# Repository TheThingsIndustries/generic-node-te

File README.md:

# Generic Node Tracker Edition (GNTE)

## About

The Generic Node Tracker Edition provides a reference HW design that features [Semtech LR1110](https://www.semtech.com/products/wireless-rf/lora-edge/lr1110) modem and an STM32L073 host MCU.

This repository contains all the necessary hardware and software files for the GNTE node.

## Documentation

The [Generic Node documentation website](https://www.genericnode.com/docs/) provides information about the node hardware and software features.

## Acknowledgment

The [Software](./Software) featured in this repository is a fork of Semtech [lr1110_modem_application_example](https://github.com/Lora-net/lr1110_modem_application_example) with minor changes that reflect the HW design.

## Legal

[Generic Node license terms and conditions](./LICENSE.md) apply.

[Contact The Things Industries](https://thethingsindustries.com/contact/) for licensing.

Copyright © 2021 The Things Industries B.V.

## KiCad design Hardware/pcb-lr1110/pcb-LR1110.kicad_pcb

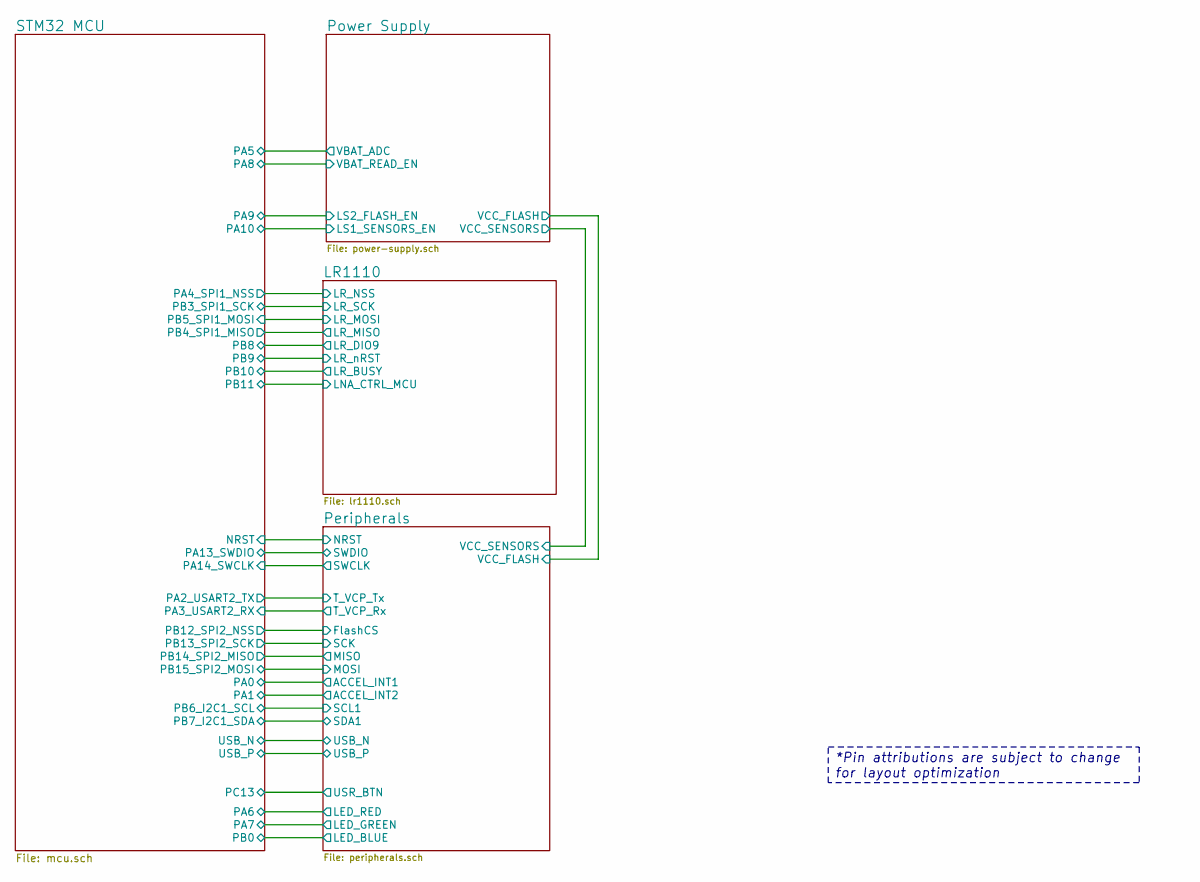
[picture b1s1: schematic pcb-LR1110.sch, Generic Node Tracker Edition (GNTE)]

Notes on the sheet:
*Pin attributions are subject to change for layout optimization

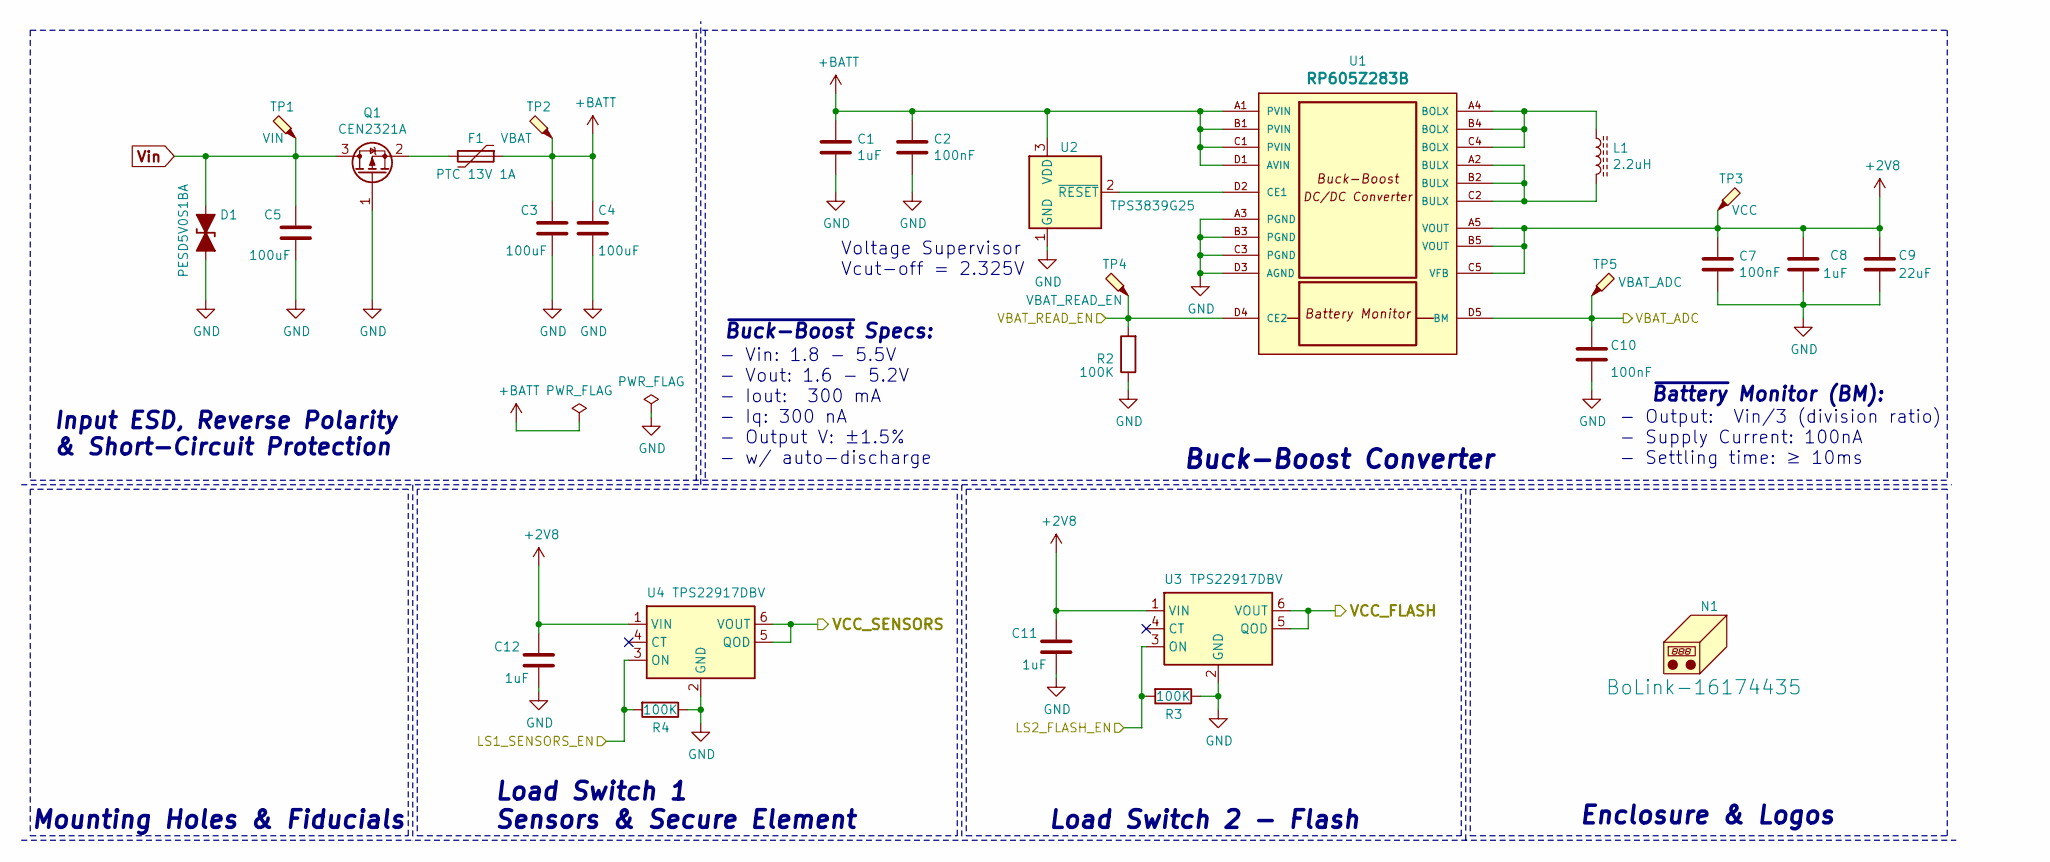
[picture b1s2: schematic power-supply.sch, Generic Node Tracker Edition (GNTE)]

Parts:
C1, C8, C11, C12: 1uF; C_0402_1005Metric; MPN CL05A105KQ5NNNC
C2, C7, C10: 100nF; C_0402_1005Metric; MPN CC0402KRX7R7BB104
C3, C4, C5: 100uF; C_1206_3216Metric; MPN JMK316ABJ107ML-T
C9: 22uF; C_0603_1608Metric; MPN CC0603MRX5R5BB226
D1: PESD5V0S1BA; D_SOD-323; MPN PESD5V0S1BA,115
F1: PTC 13V 1A; Fuse_1210_3225Metric_Castellated; MPN SMD1210-050
L1: 2.2uH; L_HPC4012TF-2R2M; MPN HPC4012TF-2R2M
N1: BoLink-16174435; BoLink_704025; MPN DNM
Q1: CEN2321A; SOT-23; MPN CEN2321A
R2, R3, R4: 100K; R_0402_1005Metric; MPN RC0402FR-07100KL
TP1: VIN; TestPoint_Pad_D1.5mm; MPN DNM
TP2: VBAT; TestPoint_Pad_D1.5mm; MPN DNM
TP3: VCC; TestPoint_Pad_D1.5mm; MPN DNM
TP4: VBAT_READ_EN; TestPoint_Pad_D1.5mm; MPN DNM
TP5: VBAT_ADC; TestPoint_Pad_D1.5mm; MPN DNM
U1: RP605Z283B; WLCSP-20-P3_1.994x1.609mm_Layout5x4_P0.4mm; MPN RP605Z283B-E2-F
U2: TPS3839G25; SOT-23; MPN TPS3839G25DBZ
U3, U4: TPS22917DBV; SOT-23-6; MPN TPS22917DBVR

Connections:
+2V8: C7.2, C8.1, C9.2, C11.1, C12.1, TP3.1, U1.A5 (VOUT), U1.B5 (VOUT), U1.C5 (VFB), U3.1 (VIN), U4.1 (VIN); also elsewhere on the board
+BATT: C1.1, C2.1, C3.2, C4.2, F1.1, TP2.1, U1.A1 (PVIN), U1.B1 (PVIN), U1.C1 (PVIN), U1.D1 (AVIN), U2.3 (VDD)
/Peripherals/VCC_FLASH: U3.5 (QOD), U3.6 (VOUT); also elsewhere on the board
/Peripherals/VCC_SENSORS: U4.5 (QOD), U4.6 (VOUT); also elsewhere on the board
/Power Supply/LS1_SENSORS_EN: R4.2, U4.3 (ON); also elsewhere on the board
/Power Supply/LS2_FLASH_EN: R3.2, U3.3 (ON); also elsewhere on the board
/STM32 MCU/PA5: C10.1, TP5.1, U1.D5 (BM); also elsewhere on the board
/STM32 MCU/PA8: R2.2, TP4.1, U1.D4 (CE2); also elsewhere on the board
GND: C1.2, C2.2, C3.1, C4.1, C5.1, C7.1, C8.2, C9.1, C10.2, C11.2, C12.2, D1.2 (A2), Q1.1 (G), R2.1, R3.1, R4.1, U1.A3 (PGND), U1.B3 (PGND), U1.C3 (PGND), U1.D3 (AGND), U2.1 (GND), U3.2 (GND), U4.2 (GND); also elsewhere on the board
unnamed: F1.2, Q1.2 (S)
unnamed: L1.1, U1.A4 (BOLX), U1.B4 (BOLX), U1.C4 (BOLX)
unnamed: L1.2, U1.A2 (BULX), U1.B2 (BULX), U1.C2 (BULX)
unnamed: U1.D2 (CE1), U2.2 (~RESET)
Vin: C5.2, D1.1 (A1), Q1.3 (D), TP1.1; also elsewhere on the board

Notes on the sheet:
Load Switch 1 Sensors & Secure Element
Load Switch 2 - Flash
Mounting Holes & Fiducials
Input ESD, Reverse Polarity & Short-Circuit Protection
Buck-Boost Converter
- Vin: 1.8 - 5.5V - Vout: 1.6 - 5.2V - Iout: 300 mA - Iq: 300 nA - Output V: ±1.5% - w/ auto-discharge
- Output: Vin/3 (division ratio) - Supply Current: 100nA - Settling time: ≥ 10ms
~Buck-Boost Specs:
~Battery Monitor (BM):
Enclosure & Logos
Voltage Supervisor Vcut-off = 2.325V

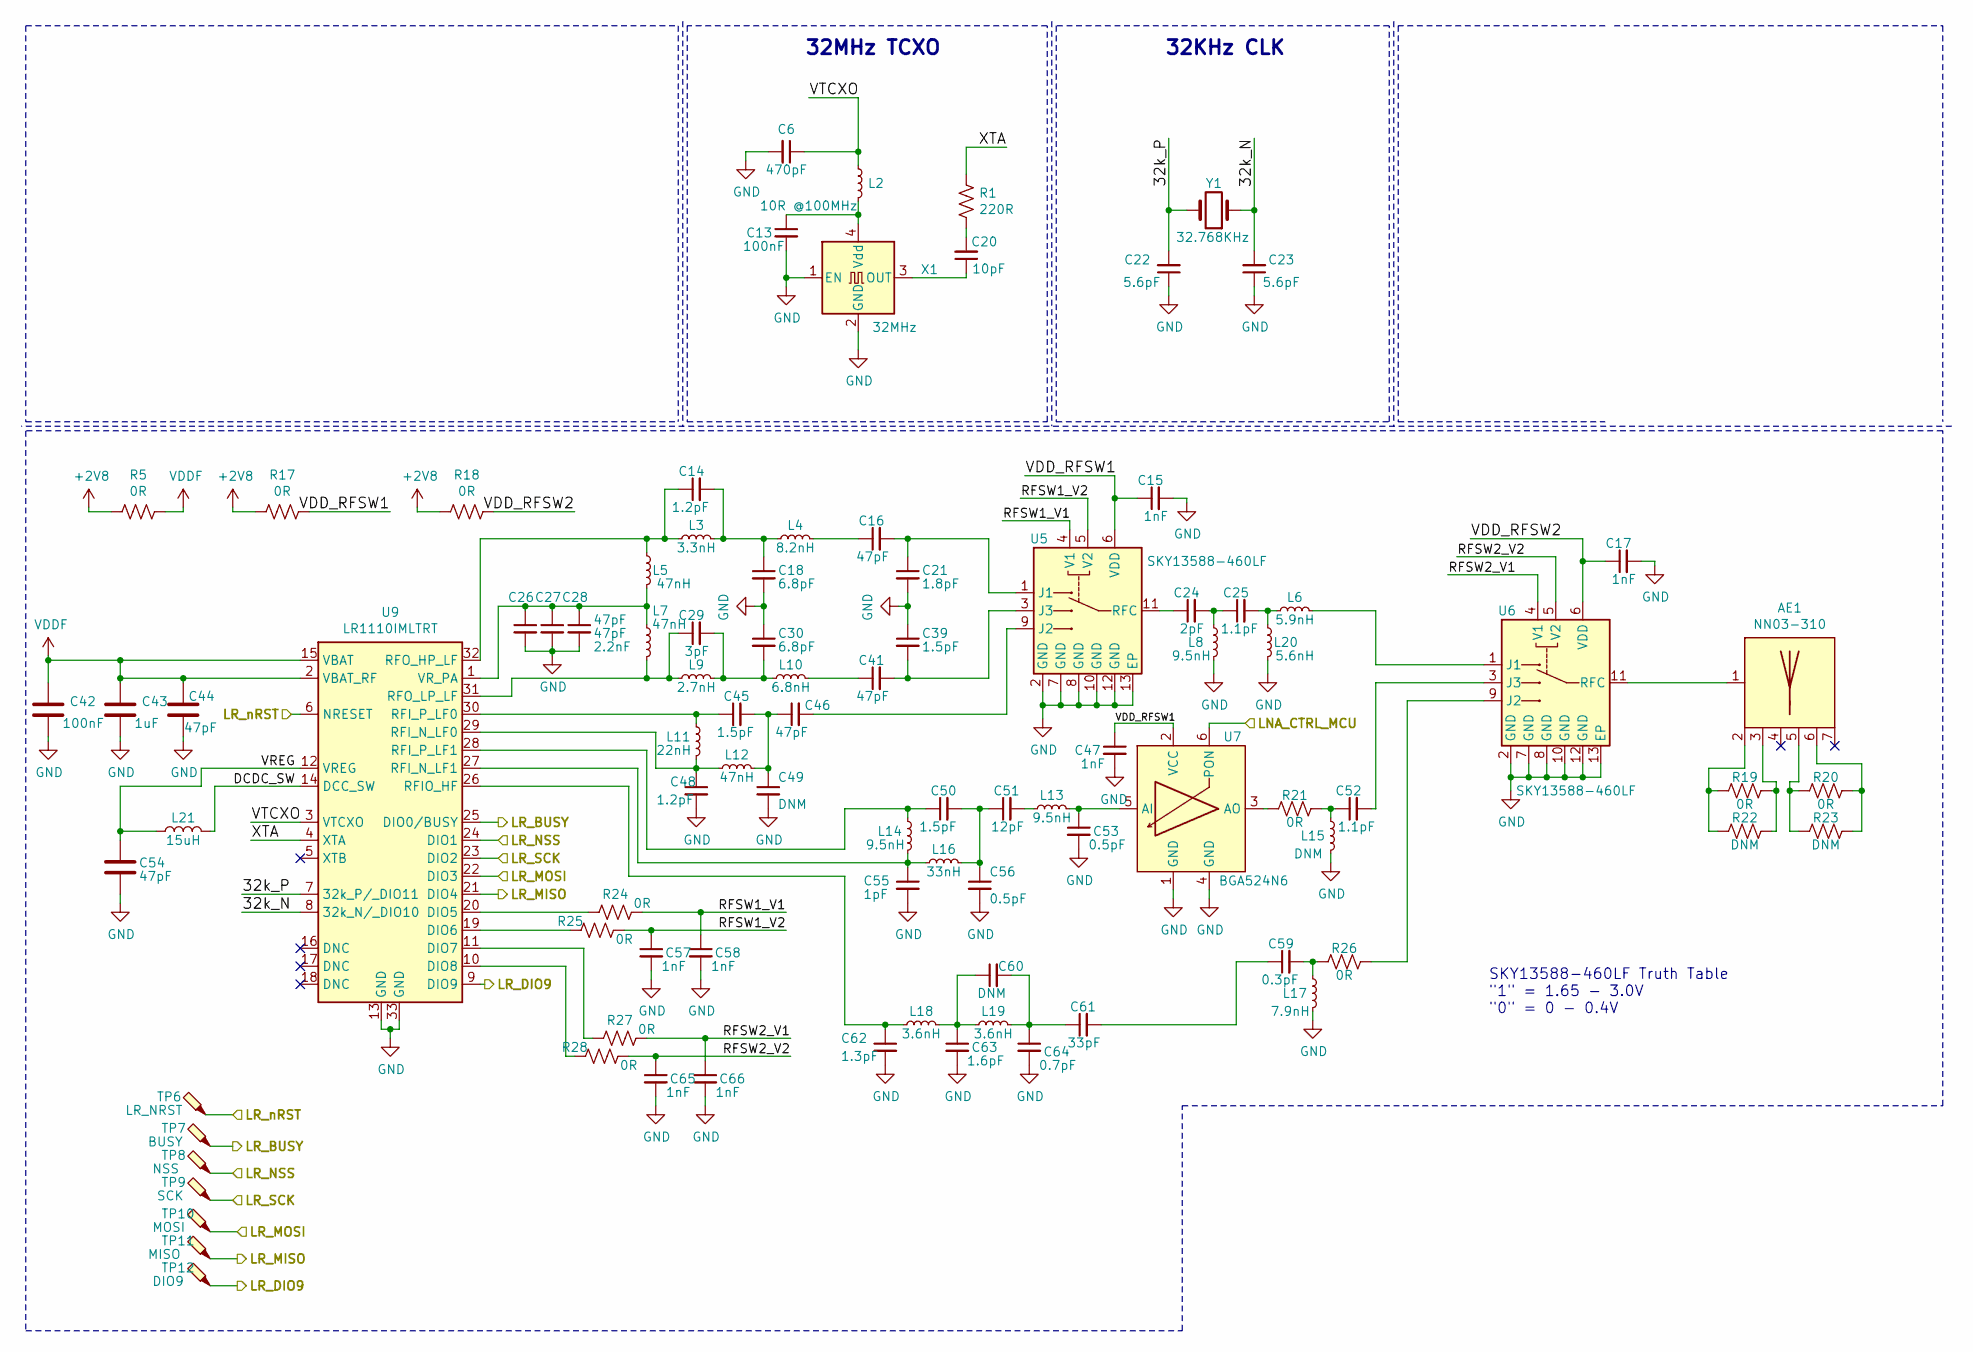
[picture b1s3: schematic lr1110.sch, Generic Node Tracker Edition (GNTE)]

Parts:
AE1: NN03-310; NN03-310_S; MPN NN03-310
C6: 470pF; C_0402_1005Metric; MPN CL05C471JO5NNNC
C13, C42: 100nF; C_0402_1005Metric; MPN CC0402KRX7R7BB104
C14, C48: 1.2pF; C_0402_1005Metric; MPN GRM1555C1H1R2BA01D
C15, C17, C47, C57, C58, C65, C66: 1nF; C_0402_1005Metric; MPN GRM155R71C102KA01D
C16, C27, C28, C41, C44, C46, C54: 47pF; C_0402_1005Metric; MPN GRM1555C1H470JA01D
C18, C30: 6.8pF; C_0402_1005Metric; MPN GRM1555C1H6R8CA01D
C20: 10pF; C_0402_1005Metric; MPN C0402C100K5RAC7867
C21: 1.8pF; C_0402_1005Metric; MPN GRM1555C1H1R8BA01D
C22, C23: 5.6pF; C_0402_1005Metric; MPN CC0402BRNPO9BN5R6
C24: 2pF; C_0402_1005Metric; MPN GJM1555C1H2R0WB01
C25, C52: 1.1pF; C_0402_1005Metric; MPN GJM1555C1H1R1WB01
C26: 2.2nF; C_0402_1005Metric; MPN GRM155R71H222KA01D
C29: 3pF; C_0402_1005Metric; MPN GRM1555C1H3R0BA01J
C39, C45, C50: 1.5pF; C_0402_1005Metric; MPN GRM1555C1H1R5BA01D
C43: 1uF; C_0402_1005Metric; MPN CL05A105KQ5NNNC
C49, C60: DNM; C_0402_1005Metric
C51: 12pF; C_0402_1005Metric; MPN GRM1555C1H120JA01D
C53, C56: 0.5pF; C_0402_1005Metric; MPN GRM1555C1HR50BA01D
C55: 1pF; C_0402_1005Metric; MPN GRM1555C1H1R0BA01D
C59: 0.3pF; C_0402_1005Metric; MPN GJM1555C1HR30WB01
C61: 33pF; C_0402_1005Metric; MPN GRM1555C1H330JA01D
C62: 1.3pF; C_0402_1005Metric; MPN GRM1555C1H1R3BA01D
C63: 1.6pF; C_0402_1005Metric; MPN GRM1555C1H1R6BA01D
C64: 0.7pF; C_0402_1005Metric; MPN GRM1555C1HR70BA01D
L2: 10R @100MHz; L_0402_1005Metric; MPN BLM15HG102SN1D
L3: 3.3nH; L_0402_1005Metric; MPN LQW15AN3N3C80D
L4: 8.2nH; L_0402_1005Metric; MPN LQW15AN8N2J00D
L5, L7, L12: 47nH; L_0402_1005Metric; MPN LQW15AN47NJ00D
L6: 5.9nH; L_0402_1005Metric; MPN LQW15AN5N9G80
L8, L13, L14: 9.5nH; L_0402_1005Metric; MPN LQW18AN9N5G80
L9: 2.7nH; L_0402_1005Metric; MPN LQW15AN2N7C00D
L10: 6.8nH; L_0402_1005Metric; MPN LQW15AN6N8J00D
L11: 22nH; L_0402_1005Metric; MPN LQW15AN22NH00D
L15: DNM; L_0402_1005Metric; MPN DNM
L16: 33nH; L_0402_1005Metric; MPN LQW15AN33NJ00D
L17: 7.9nH; L_0402_1005Metric; MPN LQW15AN7N9G80
L18, L19: 3.6nH; L_0402_1005Metric; MPN LQW15AN3N6C10D
L20: 5.6nH; L_0402_1005Metric; MPN LQW15AN5N6G80
L21: 15uH; L_0805_2012Metric; MPN MLZ2012M150W
R1: 220R; R_0402_1005Metric; MPN RC0402FR-07220RL
R5, R17, R18, R19, R20, R21, R24, R25, R26, R27, R28: 0R; R_0402_1005Metric
R22, R23: DNM; R_0402_1005Metric
TP6: LR_NRST; TestPoint_Pad_D1.0mm
TP7: BUSY; TestPoint_Pad_D1.0mm
TP8: NSS; TestPoint_Pad_D1.0mm
TP9: SCK; TestPoint_Pad_D1.0mm
TP10: MOSI; TestPoint_Pad_D1.0mm
TP11: MISO; TestPoint_Pad_D1.0mm
TP12: DIO9; TestPoint_Pad_D1.0mm
U5, U6: SKY13588-460LF; sQFN-12-1EP_2x2mm_P0.5mm_EP0.76x0.76mm; MPN SKY13588-460LF
U7: BGA524N6; TSNP-6-2-8; MPN BGA524N6
U9: LR1110IMLTRT; QFN-32-1EP_5x5mm_P0.5mm_EP3.7x3.7mm; MPN LR1110IMLTRT
X1: 32MHz; Crystal_SMD_Abracon_ABM10-4Pin_2.5x2.0mm; MPN TYETBCSANF-32.000000
Y1: 32.768KHz; Crystal_SMD_NX2012SA_32.768KHz; MPN X1A000061002100

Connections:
+2V8: R5.2, R17.2, R18.2; also elsewhere on the board
/LR1110/32k_N: C23.2, U9.8 (32k_N/_DIO10), Y1.1
/LR1110/32k_P: C22.2, U9.7 (32k_P/_DIO11), Y1.2
/LR1110/DCDC_SW: L21.2, U9.14 (DCC_SW)
/LR1110/LNA_CTRL_MCU: U7.6 (PON); also elsewhere on the board
/LR1110/LR_BUSY: TP7.1, U9.25 (DIO0/BUSY); also elsewhere on the board
/LR1110/LR_DIO9: TP12.1, U9.9 (DIO9); also elsewhere on the board
/LR1110/LR_MISO: TP11.1, U9.21 (DIO4); also elsewhere on the board
/LR1110/LR_MOSI: TP10.1, U9.22 (DIO3); also elsewhere on the board
/LR1110/LR_NSS: TP8.1, U9.24 (DIO1); also elsewhere on the board
/LR1110/LR_SCK: TP9.1, U9.23 (DIO2); also elsewhere on the board
/LR1110/LR_nRST: TP6.1, U9.6 (NRESET); also elsewhere on the board
/LR1110/RFSW1_V1: C58.1, R24.1, U5.4 (V1)
/LR1110/RFSW1_V2: C57.1, R25.1, U5.5 (V2)
/LR1110/RFSW2_V1: C66.1, R27.1, U6.4 (V1)
/LR1110/RFSW2_V2: C65.1, R28.1, U6.5 (V2)
/LR1110/VDD_RFSW1: C15.1, C47.1, R17.1, U5.6 (VDD), U7.2 (VCC)
/LR1110/VDD_RFSW2: C17.1, R18.1, U6.6 (VDD)
/LR1110/VREG: C54.1, L21.1, U9.12 (VREG)
/LR1110/VTCXO: C6.1, L2.1, U9.3 (VTCXO)
/LR1110/XTA: R1.1, U9.4 (XTA)
GND: C6.2, C13.2, C15.2, C17.2, C18.2, C21.2, C22.1, C23.1, C26.2, C27.2, C28.2, C30.1, C39.1, C42.2, C43.2, C44.2, C47.2, C48.2, C49.2, C53.2, C54.2, C55.2, C56.2, C57.2, C58.2, C62.2, C63.2, C64.2, C65.2, C66.2, L8.2, L15.2, L17.2, L20.2, U5.2 (GND), U5.7 (GND), U5.8 (GND), U5.10 (GND), U5.12 (GND), U5.13 (EP), U6.2 (GND), U6.7 (GND), U6.8 (GND), U6.10 (GND), U6.12 (GND), U6.13 (EP), U7.1 (GND), U7.4 (GND), U9.13 (GND), U9.33 (GND), X1.1 (EN), X1.2 (GND); also elsewhere on the board
unnamed: AE1.1, U6.11 (RFC)
unnamed: AE1.2, R19.2, R22.2
unnamed: AE1.3, R19.1, R22.1
unnamed: AE1.5, R20.2, R23.2
unnamed: AE1.6, R20.1, R23.1
unnamed: C13.1, L2.2, X1.4 (Vdd)
unnamed: C14.1, L3.1, L5.1, U9.32 (RFO_HP_LF)
unnamed: C14.2, C18.1, L3.2, L4.1
unnamed: C16.1, L4.2
unnamed: C16.2, C21.1, U5.1 (J1)
unnamed: C20.1, X1.3 (OUT)
unnamed: C20.2, R1.2
unnamed: C24.1, U5.11 (RFC)
unnamed: C24.2, C25.1, L8.1
unnamed: C25.2, L6.1, L20.1
unnamed: C26.1, C27.1, C28.1, L5.2, L7.1, U9.1 (VR_PA)
unnamed: C29.1, L7.2, L9.1, U9.31 (RFO_LP_LF)
unnamed: C29.2, C30.2, L9.2, L10.1
unnamed: C39.2, C41.2, U5.3 (J3)
unnamed: C41.1, L10.2
unnamed: C45.1, L11.1, U9.30 (RFI_P_LF0)
unnamed: C45.2, C46.1, C49.1, L12.2
unnamed: C46.2, U5.9 (J2)
unnamed: C48.1, L11.2, L12.1, U9.29 (RFI_N_LF0)
unnamed: C50.1, L14.1, U9.28 (RFI_P_LF1)
unnamed: C50.2, C51.1, C56.1, L16.2
unnamed: C51.2, L13.1
unnamed: C52.1, L15.1, R21.1
unnamed: C52.2, U6.3 (J3)
unnamed: C53.1, L13.2, U7.5 (AI)
unnamed: C55.1, L14.2, L16.1, U9.27 (RFI_N_LF1)
unnamed: C59.1, C61.2
unnamed: C59.2, L17.1, R26.2
unnamed: C60.1, C63.1, L18.2, L19.1
unnamed: C60.2, C61.1, C64.1, L19.2
unnamed: C62.1, L18.1, U9.26 (RFIO_HF)
unnamed: L6.2, U6.1 (J1)
unnamed: R21.2, U7.3 (AO)
unnamed: R24.2, U9.20 (DIO5)
unnamed: R25.2, U9.19 (DIO6)
unnamed: R26.1, U6.9 (J2)
unnamed: R27.2, U9.11 (DIO7)
unnamed: R28.2, U9.10 (DIO8)
VDDF: C42.1, C43.1, C44.1, R5.1, U9.2 (VBAT_RF), U9.15 (VBAT)

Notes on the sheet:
32KHz CLK
32MHz TCXO
SKY13588-460LF Truth Table "1" = 1.65 - 3.0V "0" = 0 - 0.4V

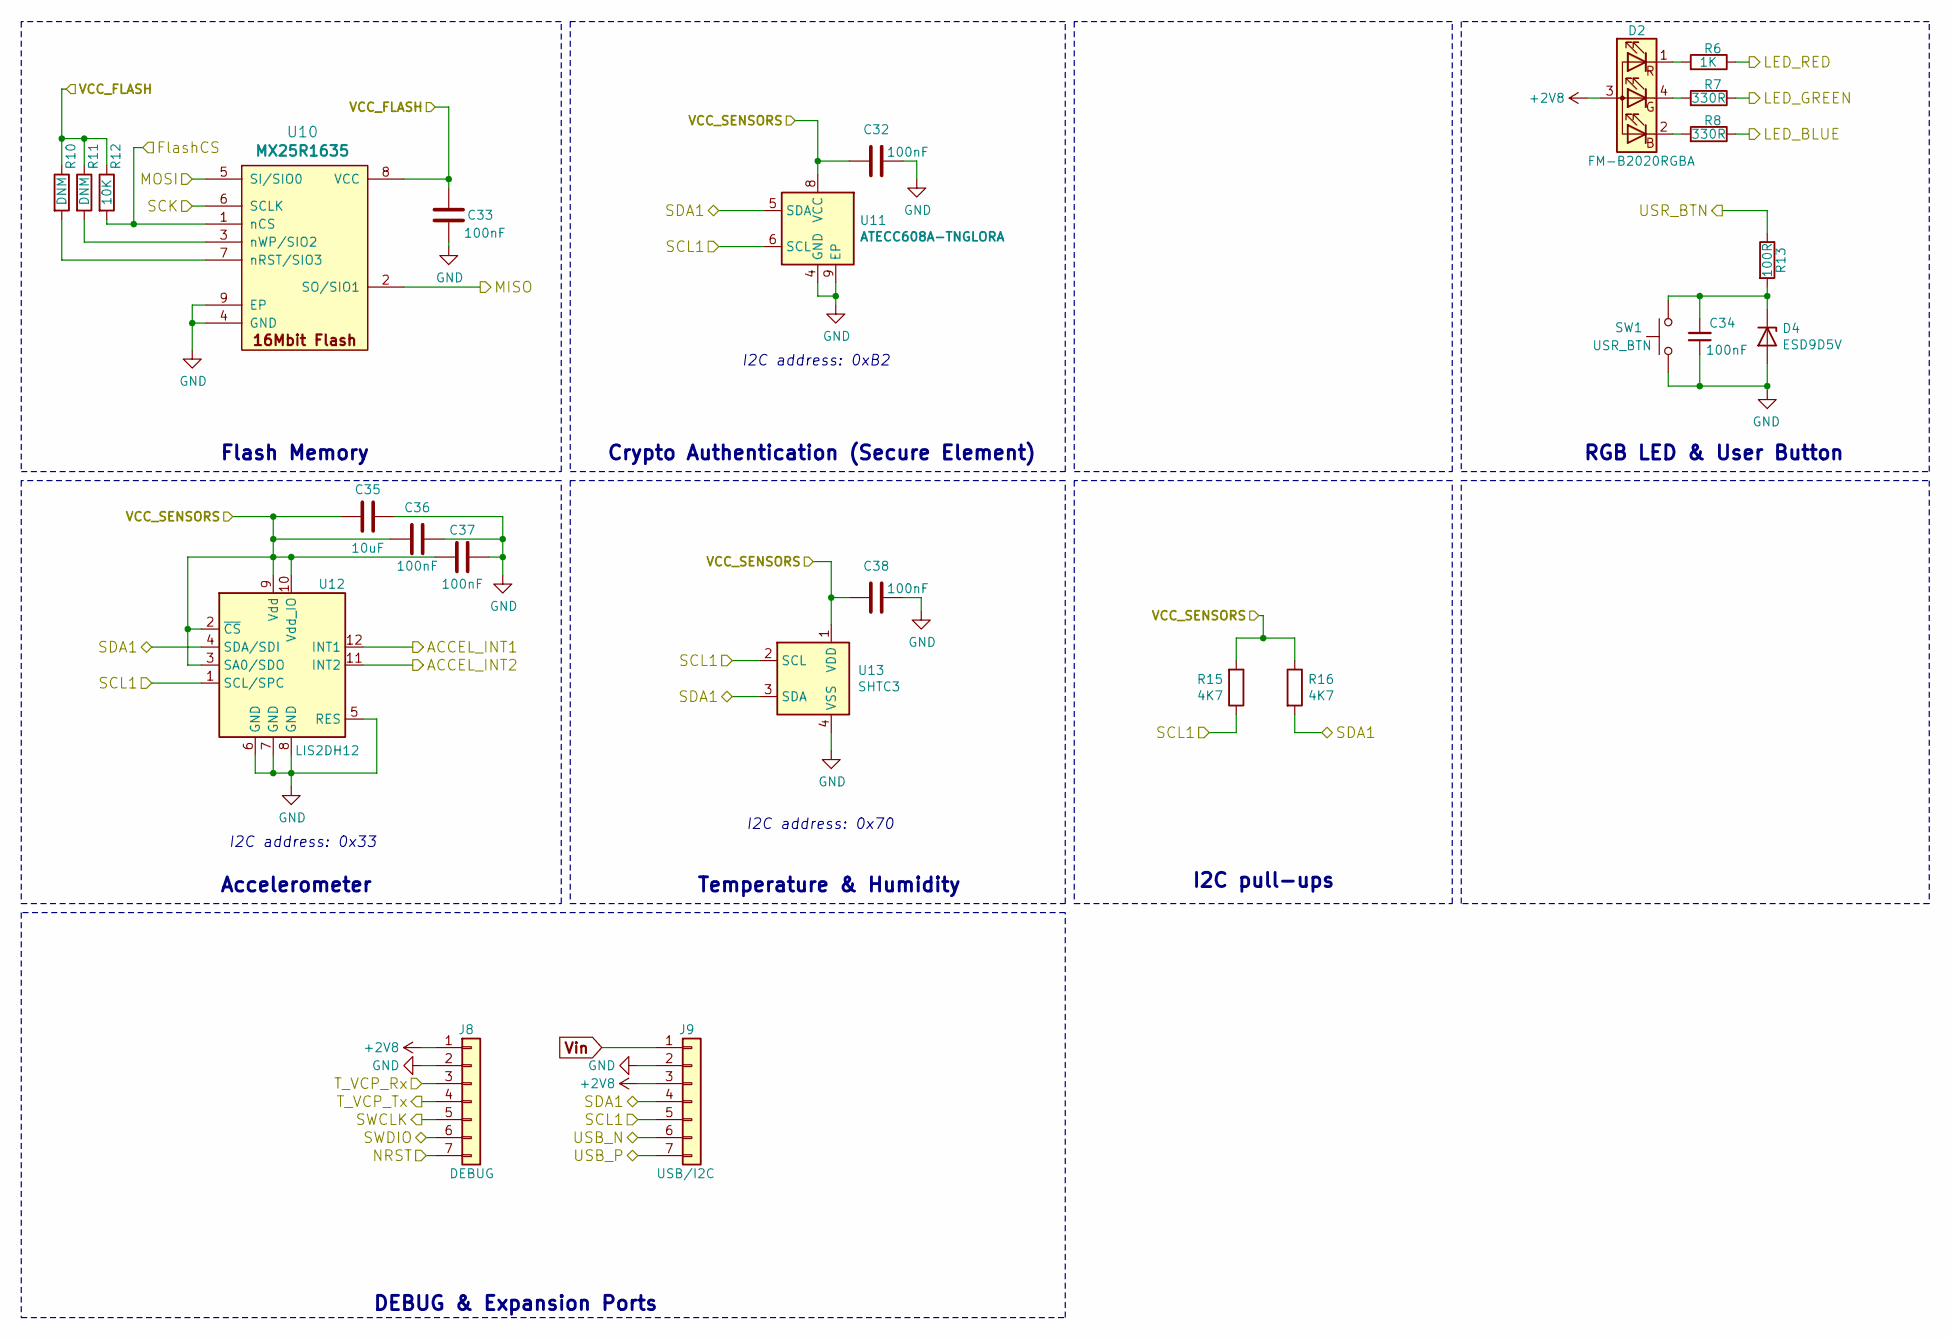
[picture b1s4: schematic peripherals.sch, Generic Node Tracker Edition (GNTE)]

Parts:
C32, C33, C34, C36, C37, C38: 100nF; C_0402_1005Metric; MPN CC0402KRX7R7BB104
C35: 10uF; C_0402_1005Metric; MPN JMK107ABJ106KA-T
D2: FM-B2020RGBA; LED_Cree-PLCC4_2x2mm_CW; MPN FM-B2020RGBA-HG
D4: ESD9D5V; D_SOD-923; MPN Diode_SMD:D_SOD-923
J8: DEBUG; PinSocket_1x07_P2.54mm_Vertical; MPN DNM
J9: USB/I2C; PinSocket_1x07_P2.54mm_Vertical; MPN DNM
R6: 1K; R_0402_1005Metric; MPN RC0402FR-071KL
R7, R8: 330R; R_0402_1005Metric; MPN AC0402FR-07330RL
R10, R11: DNM; R_0402_1005Metric; MPN DNM
R12: 10K; R_0402_1005Metric; MPN AC0402JR-0710KL
R13: 100R; R_0402_1005Metric; MPN RC0402FR-07100RL
R15, R16: 4K7; R_0402_1005Metric; MPN AC0402FR-074K7L
SW1: USR_BTN; PushButton_UK-B0234-SP25Y; MPN KSC721GLFS
U10: MX25R1635; FLASH_UFDFN-8-MX25R1635F; MPN MX25R1635FZUIL0
U11: ATECC608A-TNGLORA; DFN-8-1EP_3x2mm_P0.5mm_EP1.3x1.5mm; MPN ATECC608A-TNGLORAU-B
U12: LIS2DH12; LGA-12_2x2mm_P0.5mm; MPN LIS2DH12TR
U13: SHTC3; Sensirion_DFN-4-1EP_2x2mm_P1mm_EP0.7x1.6mm; MPN SHTC3

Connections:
+2V8: D2.3 (BK), J8.1, J9.3; also elsewhere on the board
/Peripherals/ACCEL_INT1: U12.12 (INT1); also elsewhere on the board
/Peripherals/ACCEL_INT2: U12.11 (INT2); also elsewhere on the board
/Peripherals/FlashCS: R12.2, U10.1 (nCS); also elsewhere on the board
/Peripherals/LED_BLUE: R8.1; also elsewhere on the board
/Peripherals/LED_GREEN: R7.1; also elsewhere on the board
/Peripherals/LED_RED: R6.1; also elsewhere on the board
/Peripherals/MISO: U10.2 (SO/SIO1); also elsewhere on the board
/Peripherals/MOSI: U10.5 (SI/SIO0); also elsewhere on the board
/Peripherals/NRST: J8.7; also elsewhere on the board
/Peripherals/USB_N: J9.6; also elsewhere on the board
/Peripherals/USB_P: J9.7; also elsewhere on the board
/Peripherals/VCC_FLASH: C33.2, R10.1, R11.1, R12.1, U10.8 (VCC); also elsewhere on the board
/Peripherals/VCC_SENSORS: C32.2, C35.2, C36.2, C37.2, C38.2, R15.2, R16.1, U11.8 (VCC), U12.2 (~CS), U12.3 (SA0/SDO), U12.9 (Vdd), U12.10 (Vdd_IO), U13.1 (VDD); also elsewhere on the board
/STM32 MCU/PA2_USART2_TX: J8.4; also elsewhere on the board
/STM32 MCU/PA3_USART2_RX: J8.3; also elsewhere on the board
/STM32 MCU/PA13_SWDIO: J8.6; also elsewhere on the board
/STM32 MCU/PA14_SWCLK: J8.5; also elsewhere on the board
/STM32 MCU/PB6_I2C1_SCL: J9.5, R15.1, U11.6 (SCL), U12.1 (SCL/SPC), U13.2 (SCL); also elsewhere on the board
/STM32 MCU/PB7_I2C1_SDA: J9.4, R16.2, U11.5 (SDA), U12.4 (SDA/SDI), U13.3 (SDA); also elsewhere on the board
/STM32 MCU/PB13_SPI2_SCK: U10.6 (SCLK); also elsewhere on the board
/STM32 MCU/PC13: R13.1; also elsewhere on the board
GND: C32.1, C33.1, C34.1, C35.1, C36.1, C37.1, C38.1, D4.2 (A), J8.2, J9.2, SW1.2, U10.4 (GND), U10.9 (EP), U11.4 (GND), U11.9 (EP), U12.5 (RES), U12.6 (GND), U12.7 (GND), U12.8 (GND), U13.4 (VSS); also elsewhere on the board
unnamed: C34.2, D4.1 (K), R13.2, SW1.1
unnamed: D2.1 (RK), R6.2
unnamed: D2.2 (GK), R8.2
unnamed: D2.4 (A), R7.2
unnamed: R10.2, U10.7 (nRST/SIO3)
unnamed: R11.2, U10.3 (nWP/SIO2)
Vin: J9.1; also elsewhere on the board

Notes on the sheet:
I2C address: 0x33
Accelerometer
Flash Memory
Crypto Authentication (Secure Element)
RGB LED & User Button
I2C address: 0xB2
Temperature & Humidity
I2C address: 0x70
I2C pull-ups
DEBUG & Expansion Ports

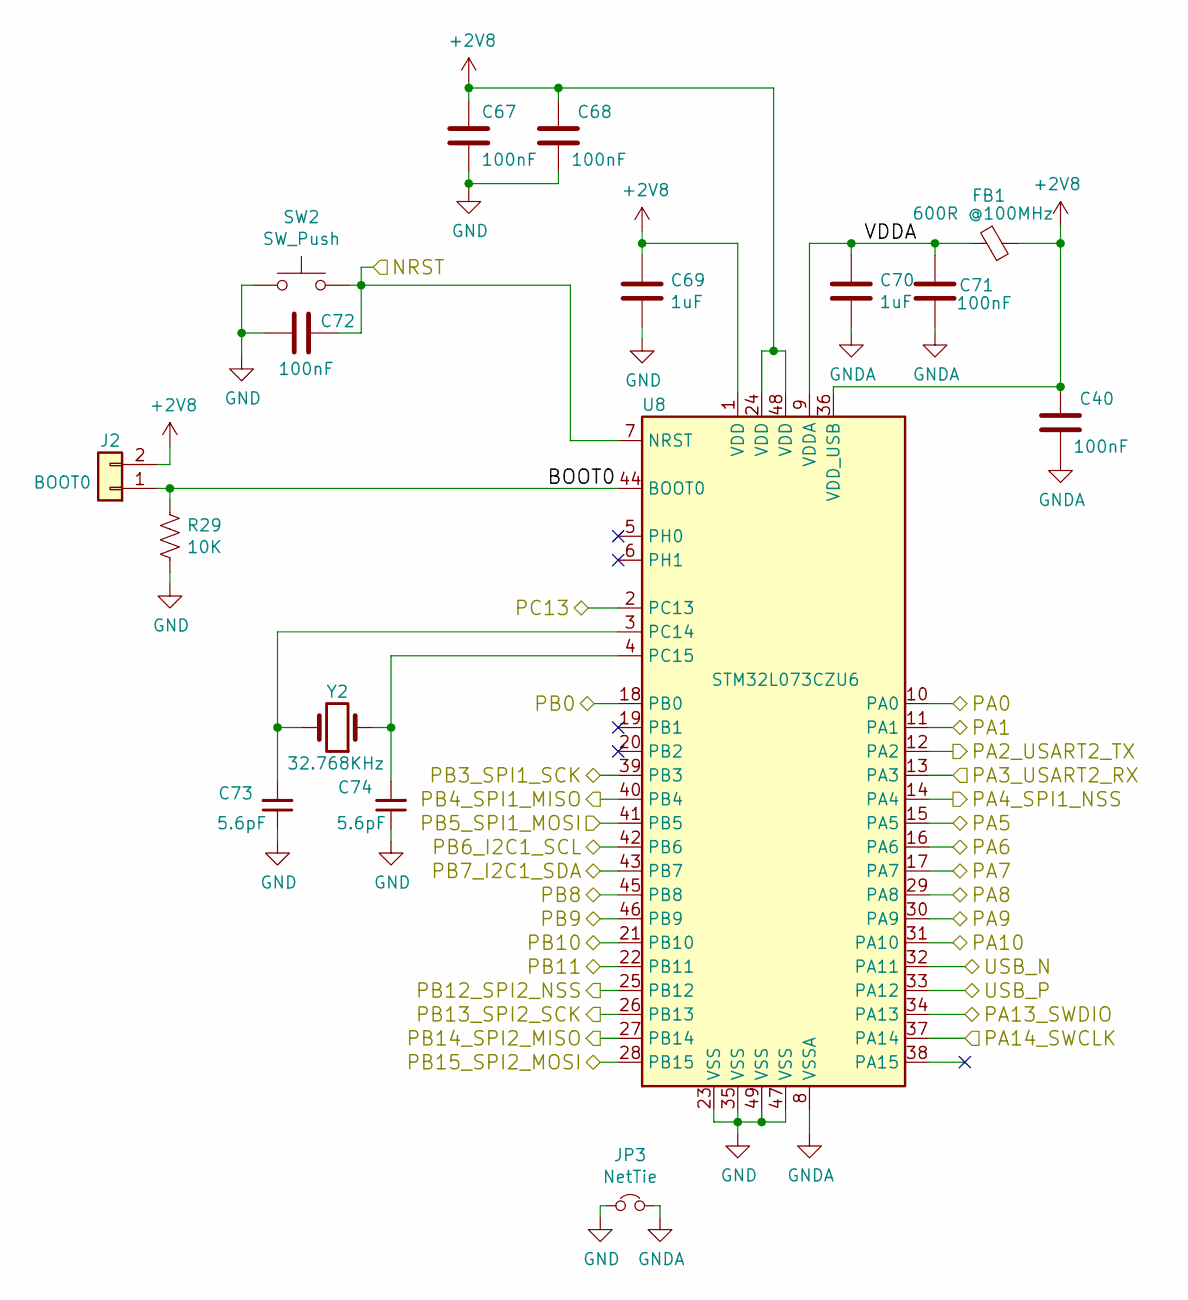
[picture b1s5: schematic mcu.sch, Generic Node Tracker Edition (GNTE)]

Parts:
C40, C67, C68, C71, C72: 100nF; C_0402_1005Metric; MPN CC0402KRX7R7BB104
C69, C70: 1uF; C_0402_1005Metric; MPN CL05A105KQ5NNNC
C73, C74: 5.6pF; C_0402_1005Metric; MPN CC0402BRNPO9BN5R6
FB1: 600R @100MHz; L_0603_1608Metric; MPN BLM18AG601SN1D
J2: BOOT0; PinHeader_1x02_P1.27mm_Vertical; MPN DNM
JP3: NetTie; SolderJumper-2_P1.3mm_Bridged2Bar_Pad1.0x1.5mm; MPN DNM
R29: 10K; R_0402_1005Metric
SW2: SW_Push; SW_SPST_SKSHABE010
U8: STM32L073CZU6; QFN-48-1EP_7x7mm_P0.5mm_EP5.45x5.45mm; MPN STM32L073CZU6
Y2: 32.768KHz; Crystal_SMD_NX2012SA_32.768KHz; MPN X1A000061002100

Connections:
+2V8: C40.1, C67.1, C68.1, C69.1, FB1.2, J2.2, U8.1 (VDD), U8.24 (VDD), U8.36 (VDD_USB), U8.48 (VDD); also elsewhere on the board
/LR1110/LNA_CTRL_MCU: U8.22 (PB11); also elsewhere on the board
/LR1110/LR_BUSY: U8.21 (PB10); also elsewhere on the board
/LR1110/LR_DIO9: U8.45 (PB8); also elsewhere on the board
/LR1110/LR_MISO: U8.40 (PB4); also elsewhere on the board
/LR1110/LR_MOSI: U8.41 (PB5); also elsewhere on the board
/LR1110/LR_NSS: U8.14 (PA4); also elsewhere on the board
/LR1110/LR_SCK: U8.39 (PB3); also elsewhere on the board
/LR1110/LR_nRST: U8.46 (PB9); also elsewhere on the board
/Peripherals/ACCEL_INT1: U8.10 (PA0); also elsewhere on the board
/Peripherals/ACCEL_INT2: U8.11 (PA1); also elsewhere on the board
/Peripherals/FlashCS: U8.25 (PB12); also elsewhere on the board
/Peripherals/LED_BLUE: U8.18 (PB0); also elsewhere on the board
/Peripherals/LED_GREEN: U8.17 (PA7); also elsewhere on the board
/Peripherals/LED_RED: U8.16 (PA6); also elsewhere on the board
/Peripherals/MISO: U8.27 (PB14); also elsewhere on the board
/Peripherals/MOSI: U8.28 (PB15); also elsewhere on the board
/Peripherals/NRST: C72.1, SW2.2, U8.7 (NRST); also elsewhere on the board
/Peripherals/USB_N: U8.32 (PA11); also elsewhere on the board
/Peripherals/USB_P: U8.33 (PA12); also elsewhere on the board
/Power Supply/LS1_SENSORS_EN: U8.31 (PA10); also elsewhere on the board
/Power Supply/LS2_FLASH_EN: U8.30 (PA9); also elsewhere on the board
/STM32 MCU/BOOT0: J2.1, R29.1, U8.44 (BOOT0)
/STM32 MCU/PA2_USART2_TX: U8.12 (PA2); also elsewhere on the board
/STM32 MCU/PA3_USART2_RX: U8.13 (PA3); also elsewhere on the board
/STM32 MCU/PA5: U8.15 (PA5); also elsewhere on the board
/STM32 MCU/PA8: U8.29 (PA8); also elsewhere on the board
/STM32 MCU/PA13_SWDIO: U8.34 (PA13); also elsewhere on the board
/STM32 MCU/PA14_SWCLK: U8.37 (PA14); also elsewhere on the board
/STM32 MCU/PB6_I2C1_SCL: U8.42 (PB6); also elsewhere on the board
/STM32 MCU/PB7_I2C1_SDA: U8.43 (PB7); also elsewhere on the board
/STM32 MCU/PB13_SPI2_SCK: U8.26 (PB13); also elsewhere on the board
/STM32 MCU/PC13: U8.2 (PC13); also elsewhere on the board
/STM32 MCU/VDDA: C70.1, C71.1, FB1.1, U8.9 (VDDA)
GND: C67.2, C68.2, C69.2, C72.2, C73.1, C74.1, JP3.1, R29.2, SW2.1, U8.23 (VSS), U8.35 (VSS), U8.47 (VSS), U8.49 (VSS); also elsewhere on the board
GNDA: C40.2, C70.2, C71.2, JP3.2, U8.8 (VSSA)
unnamed: C73.2, U8.3 (PC14), Y2.2
unnamed: C74.2, U8.4 (PC15), Y2.1
